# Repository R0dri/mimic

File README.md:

Welcome to MIMIC repository, PCB files for the prosthetic arm are located at pcb folder

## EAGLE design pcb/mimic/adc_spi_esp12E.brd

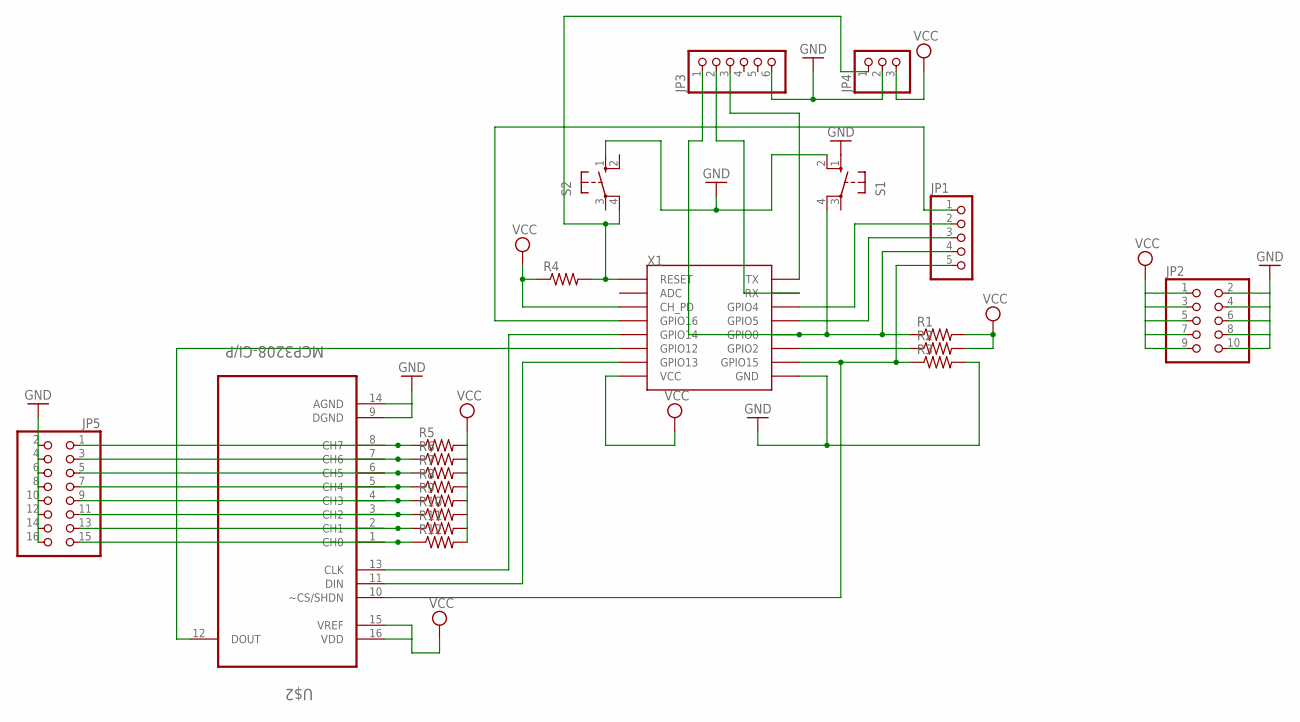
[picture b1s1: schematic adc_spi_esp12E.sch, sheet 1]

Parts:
JP1: PINHD-1X5; 1X05
JP2: PINHD-2X5; 2X05
JP3: PINHD-1X6B; 1X06-BIG
JP4: PINHD-1X3; 1X03
JP5: PINHD-2X8; 2X08
R1, R2, R3, R4, R5, R6, R7, R8, R9, R10, R11, R12: R-US_0204/7; 0204/7
S1, S2: 10-XX; B3F-10XX
U$2: MCP3208-CI/P; DIP254P762X432-16
X1: ESP12SMD; ESP12-SMD

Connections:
GND: JP2.2, JP2.4, JP2.6, JP2.8, JP2.10, JP3.6, JP4.2, JP5.2, JP5.4, JP5.6, JP5.8, JP5.10, JP5.12, JP5.14, JP5.16, R3.2, S1.1 (S), S1.2 (S1), S2.1 (S), U$2.9 (DGND), U$2.14 (AGND), X1.GND
unnamed: JP1.2, X1.GPIO4
unnamed: R2.1, X1.GPIO2
unnamed: JP1.1, X1.GPIO16
unnamed: U$2.13 (CLK), X1.GPIO14
unnamed: U$2.11 (DIN), X1.GPIO13
unnamed: U$2.12 (DOUT), X1.GPIO12
unnamed: JP4.1, R4.2, S2.4 (P1), X1.RESET
unnamed: JP1.3, X1.GPIO5
unnamed: JP1.4, JP3.1, R1.1, S1.4 (P1), X1.GPIO0
unnamed: JP3.3, X1.TXD0 (TX)
unnamed: JP1.5, R3.1, U$2.10 (~CS/SHDN), X1.GPIO15
unnamed: JP3.2, X1.RXD0 (RX)
unnamed: JP5.1, R5.1, U$2.8 (CH7)
unnamed: JP5.3, R6.1, U$2.7 (CH6)
unnamed: JP5.5, R7.1, U$2.6 (CH5)
unnamed: JP5.7, R8.1, U$2.5 (CH4)
unnamed: JP5.9, R9.1, U$2.4 (CH3)
unnamed: JP5.11, R10.1, U$2.3 (CH2)
unnamed: JP5.13, R11.1, U$2.2 (CH1)
unnamed: JP5.15, R12.1, U$2.1 (CH0)
VCC: JP2.1, JP2.3, JP2.5, JP2.7, JP2.9, JP4.3, R1.2, R2.2, R4.1, R5.2, R6.2, R7.2, R8.2, R9.2, R10.2, R11.2, R12.2, U$2.15 (VREF), U$2.16 (VDD), X1.CH_PD, X1.VCC

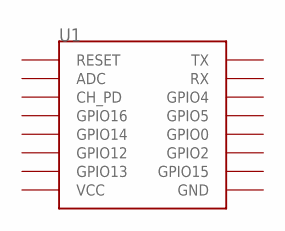
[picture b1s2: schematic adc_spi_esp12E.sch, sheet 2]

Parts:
U1: ESP12SMD; ESP12-SMD

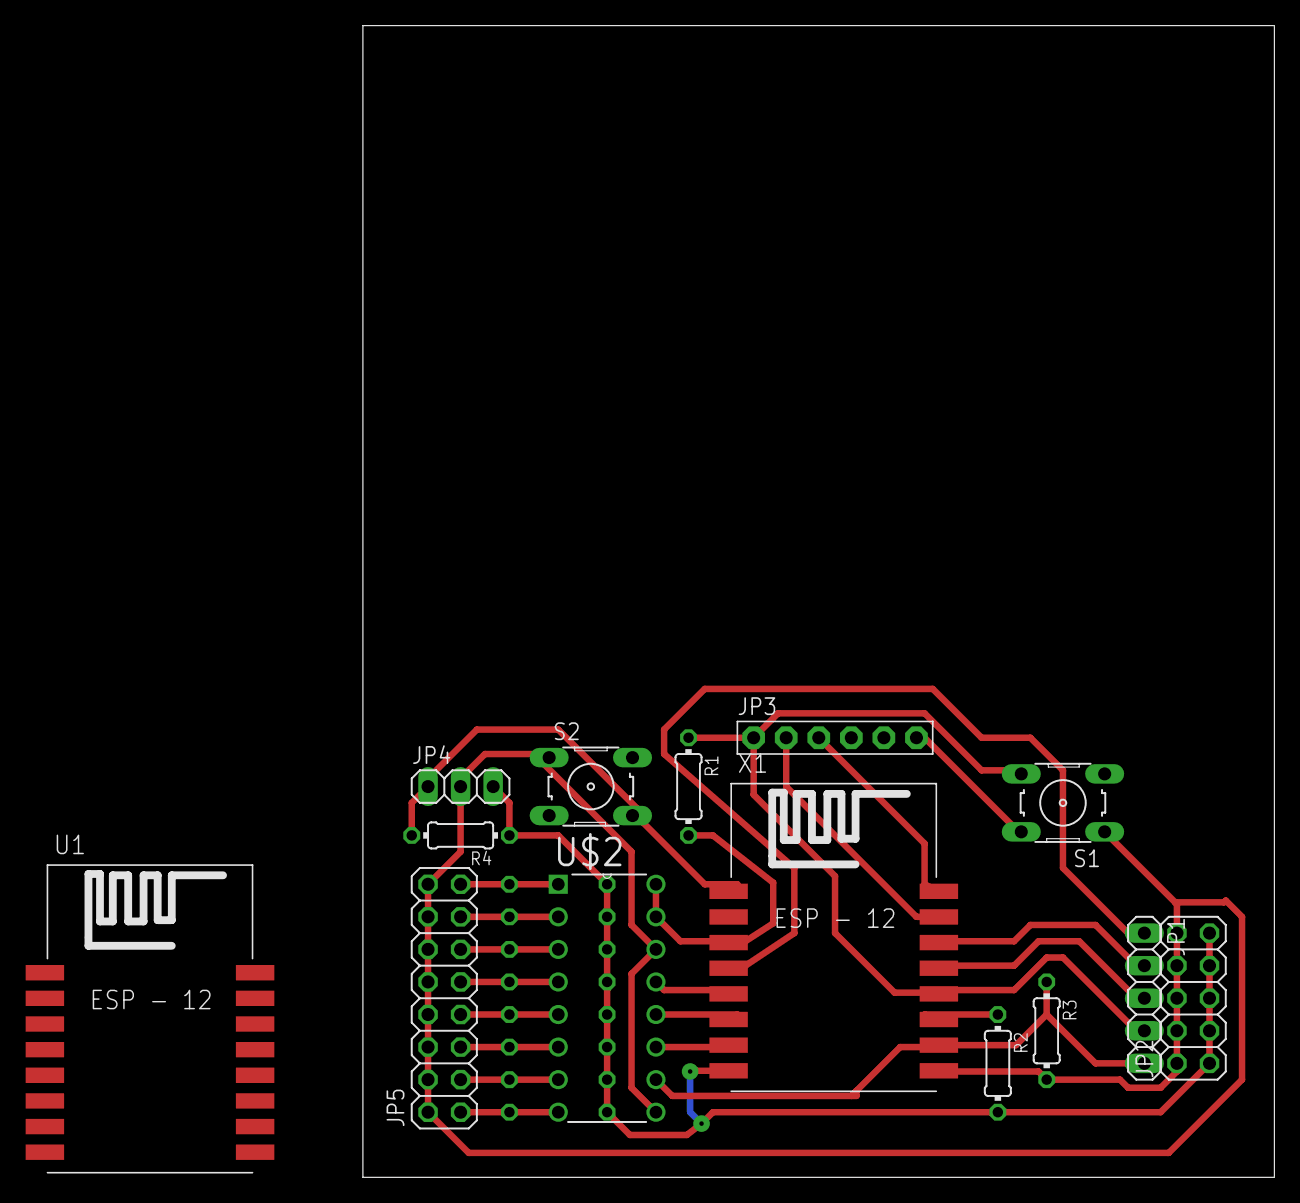
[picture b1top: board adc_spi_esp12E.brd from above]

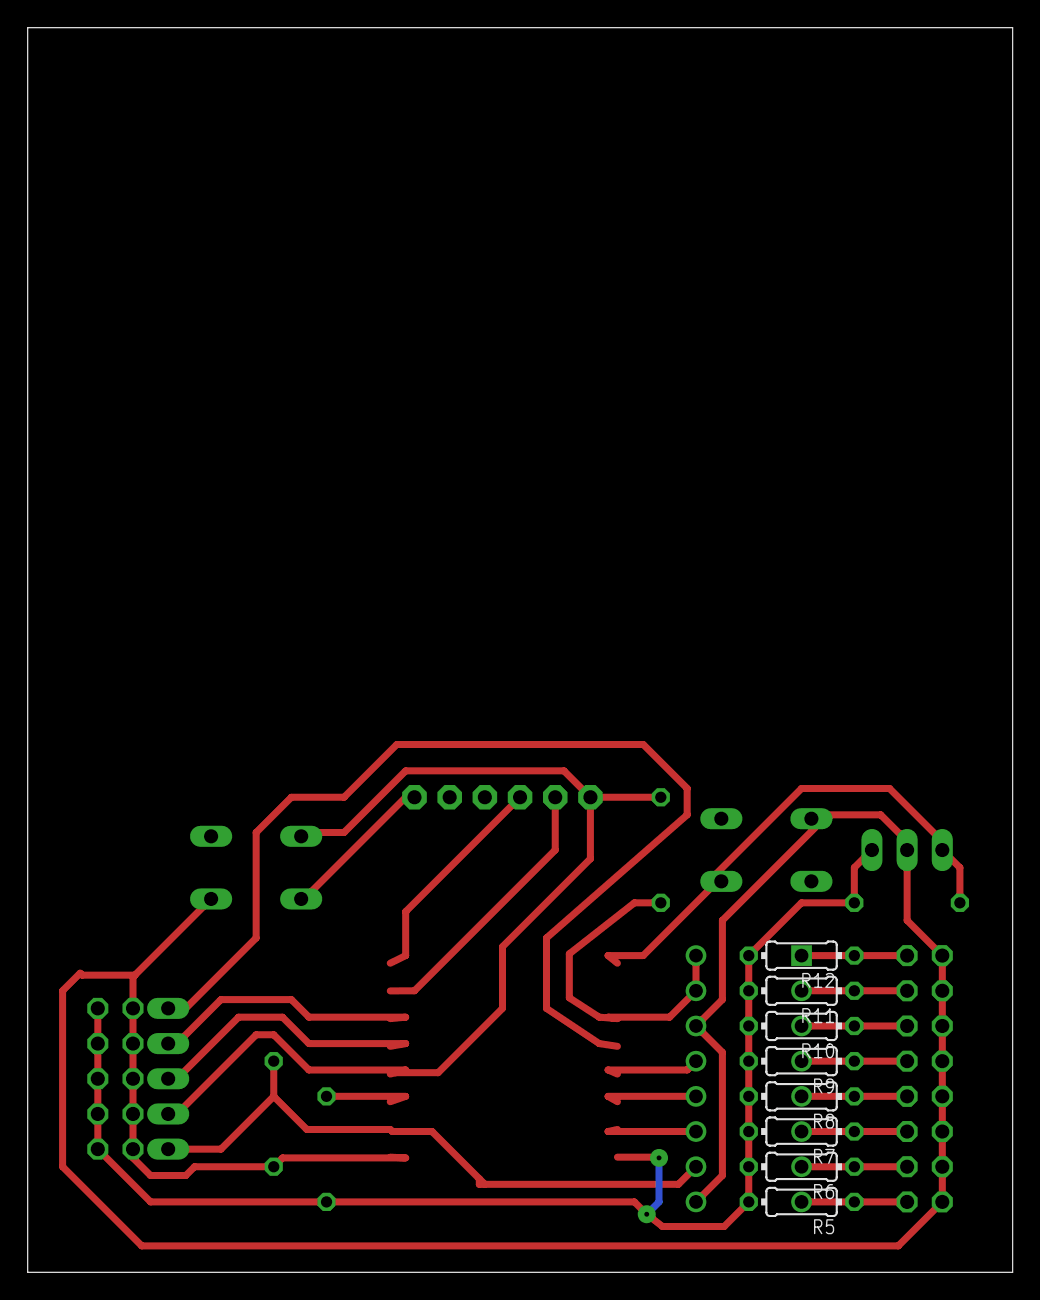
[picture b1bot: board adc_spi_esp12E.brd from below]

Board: 2 copper layers, 71.1 x 89.8 mm, 22 parts (8 on the bottom side), 22 nets.

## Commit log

2018-08-21 added .pdf .bpm of board and deleted garbage.
2018-08-21 clean up
